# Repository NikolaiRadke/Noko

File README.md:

The DIY-**Noko Monster**, lovely and naughty, ready to build on your own. And everyone is invited to **contribute**. Noko is for everyone. What's new? See the [newsblog](https://github.com/NikolaiRadke/Noko/tree/master/NEWS.md).  

> [!NOTE]
> This Repository is not maintained anymore. 

Noko is a multifunctional monster with an ATmega328  microcontroller on an **Arduino Nano**, display, clock, radio, mp3 player, four buttons as user interface, battery, voice set and  tons of gimmicks, packed in a cuddly monster suit - sturdy,
lovely and sometimes a bit mean and annoying. Just the way you want him to be. He, she or it - this is your decision     and only depends on the voice set. In this repository Noko is a lad, a real bloke! A buddy for life and a companion by day and night. All he needs is a little power every now and then.  

**Noko** stands for **No**ra and ni**ko**'s monster.

### Notes for non-German Noko makers
There are a German and an English version. Right now, the building wiki, the voice set, the manual and the optional EEPROM text files are in German. I'll try to translate the wiki and the manual one day. Until then, feel free to ask me for translation, if you need help. **Contribute!** I need an English voice set and English text files. In addition, any other language is welcome, Noko is to be cosmopolitan!

### Prerequisites
Noko needs Arduino IDE 1.6.6 - [1.8.2](https://www.arduino.cc/en/Main/Software) Copy the folder `Noko/V10/src/[language]/Noko/` into your sketch folder. When using 1.6.10 or newer with AVR core 1.6.12 or newer, everything will compile out-of-the-box. With 1.6.9 or lower, *Noko.ino* won't compile, the sketch size is too large. 

**Option 1:** Install newest  [IDE](https://www.arduino.cc/en/Main/Software) and relax.  
**Option 2:** If you are using IDE 1.6.9 or lower, you need to install [Optiboot](https://github.com/Optiboot/optiboot) onto your Nano.  
**Option 3:** Take one of the precompiled hex-files and follow the instructions in [how to compile](https://github.com/NikolaiRadke/Noko/tree/master/howto_compile).  

**In any case, Optiboot is strongly recommended.**

### Content

```
Noko/
├── howto_compile/
|   Manual how compile the sketches in your Arduino IDE and precompiled sketches.  
|   └── precompiled/
|       Precompiled hex-files and windows tools.
|       ├── Deutsch/
|       |   German Versions.
|       ├── English/
|       |   English Versions.
|       ├── Flashtool/
|       |   Linux firmware flasher.
|       └── avrdude_win/
|           Avrdude files for windows.
|
├── manual/
|   Noko manual in PDF format and a template for a packaging design.
|   └── scribus/
|       Source documents for Scribus with all illustrations and fonts.
|
├── mp3/
|   Female and male voice sets for Noko in German. English needed? Contribute!
|   ├── female/  
|   |   Female voice set for Nokos.
|   |   └── VoiceSet_226/
|   |       New voice files.
|   └── male/
|       Male voice sets
|       ├── alternative/
|       |   Some less rude voice files.
|       ├── VoiceSet_111/
|       |   Voice set for older Nokos.
|       └── VoiceSet_226/
|           Enhanced voice set.
| 
├── schematics/
|   The Schematics for the Noko parts, the Noko sewing pattern and shopping lists.
|   └── geda/
|       Source documents for gEDA.
|
├── src/
|   Arduino sketches.
|   ├── deutsch/
|   |   German version
|   |   └── Noko/
|   |       Main sourcecode with all the required libraries.
|   ├── english/
|   |   English version. 
|   |   └── Noko/
|   |       Same files but translated. 
|   └── tools/
|       Tools for using components and diagnostic.    
|       ├── I2C-Scanner/
|       |   Sketch to scan adresses of all connected I2C-devices.
|       ├── Noko_Diagnostics/
|       |   Tool to test Noko functions via serial monitor.
|       ├── Noko_Disk1/
|       |   Sketch to write the Disk1 textfile into 24LC256-EEPROMs.
|       ├── Noko_EEPROM_Disk0/
|       |   Sketch to write Noko presets into the Arduino EEPROM and the Disk0 textfile into the
|       |   AH24C32 EEPROM.
|       └── Noko_Time/
|           Simple tool to set the current time without touching the EEPROM
└── write_EEPROM/
    Tools to write data through serial connection to the Arduino and the EEPROMs. 
```
### Let's get started!

Interested in Noko? Great! Let's start here: [German wiki](https://github.com/NikolaiRadke/Noko/wiki).  
English wiki will follow. One day...

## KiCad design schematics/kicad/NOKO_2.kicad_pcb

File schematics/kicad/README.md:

Achtung! Bitte die Gerber Dateien noch nicht benutzen! Es müssen noch Fehler beseitigt werden.

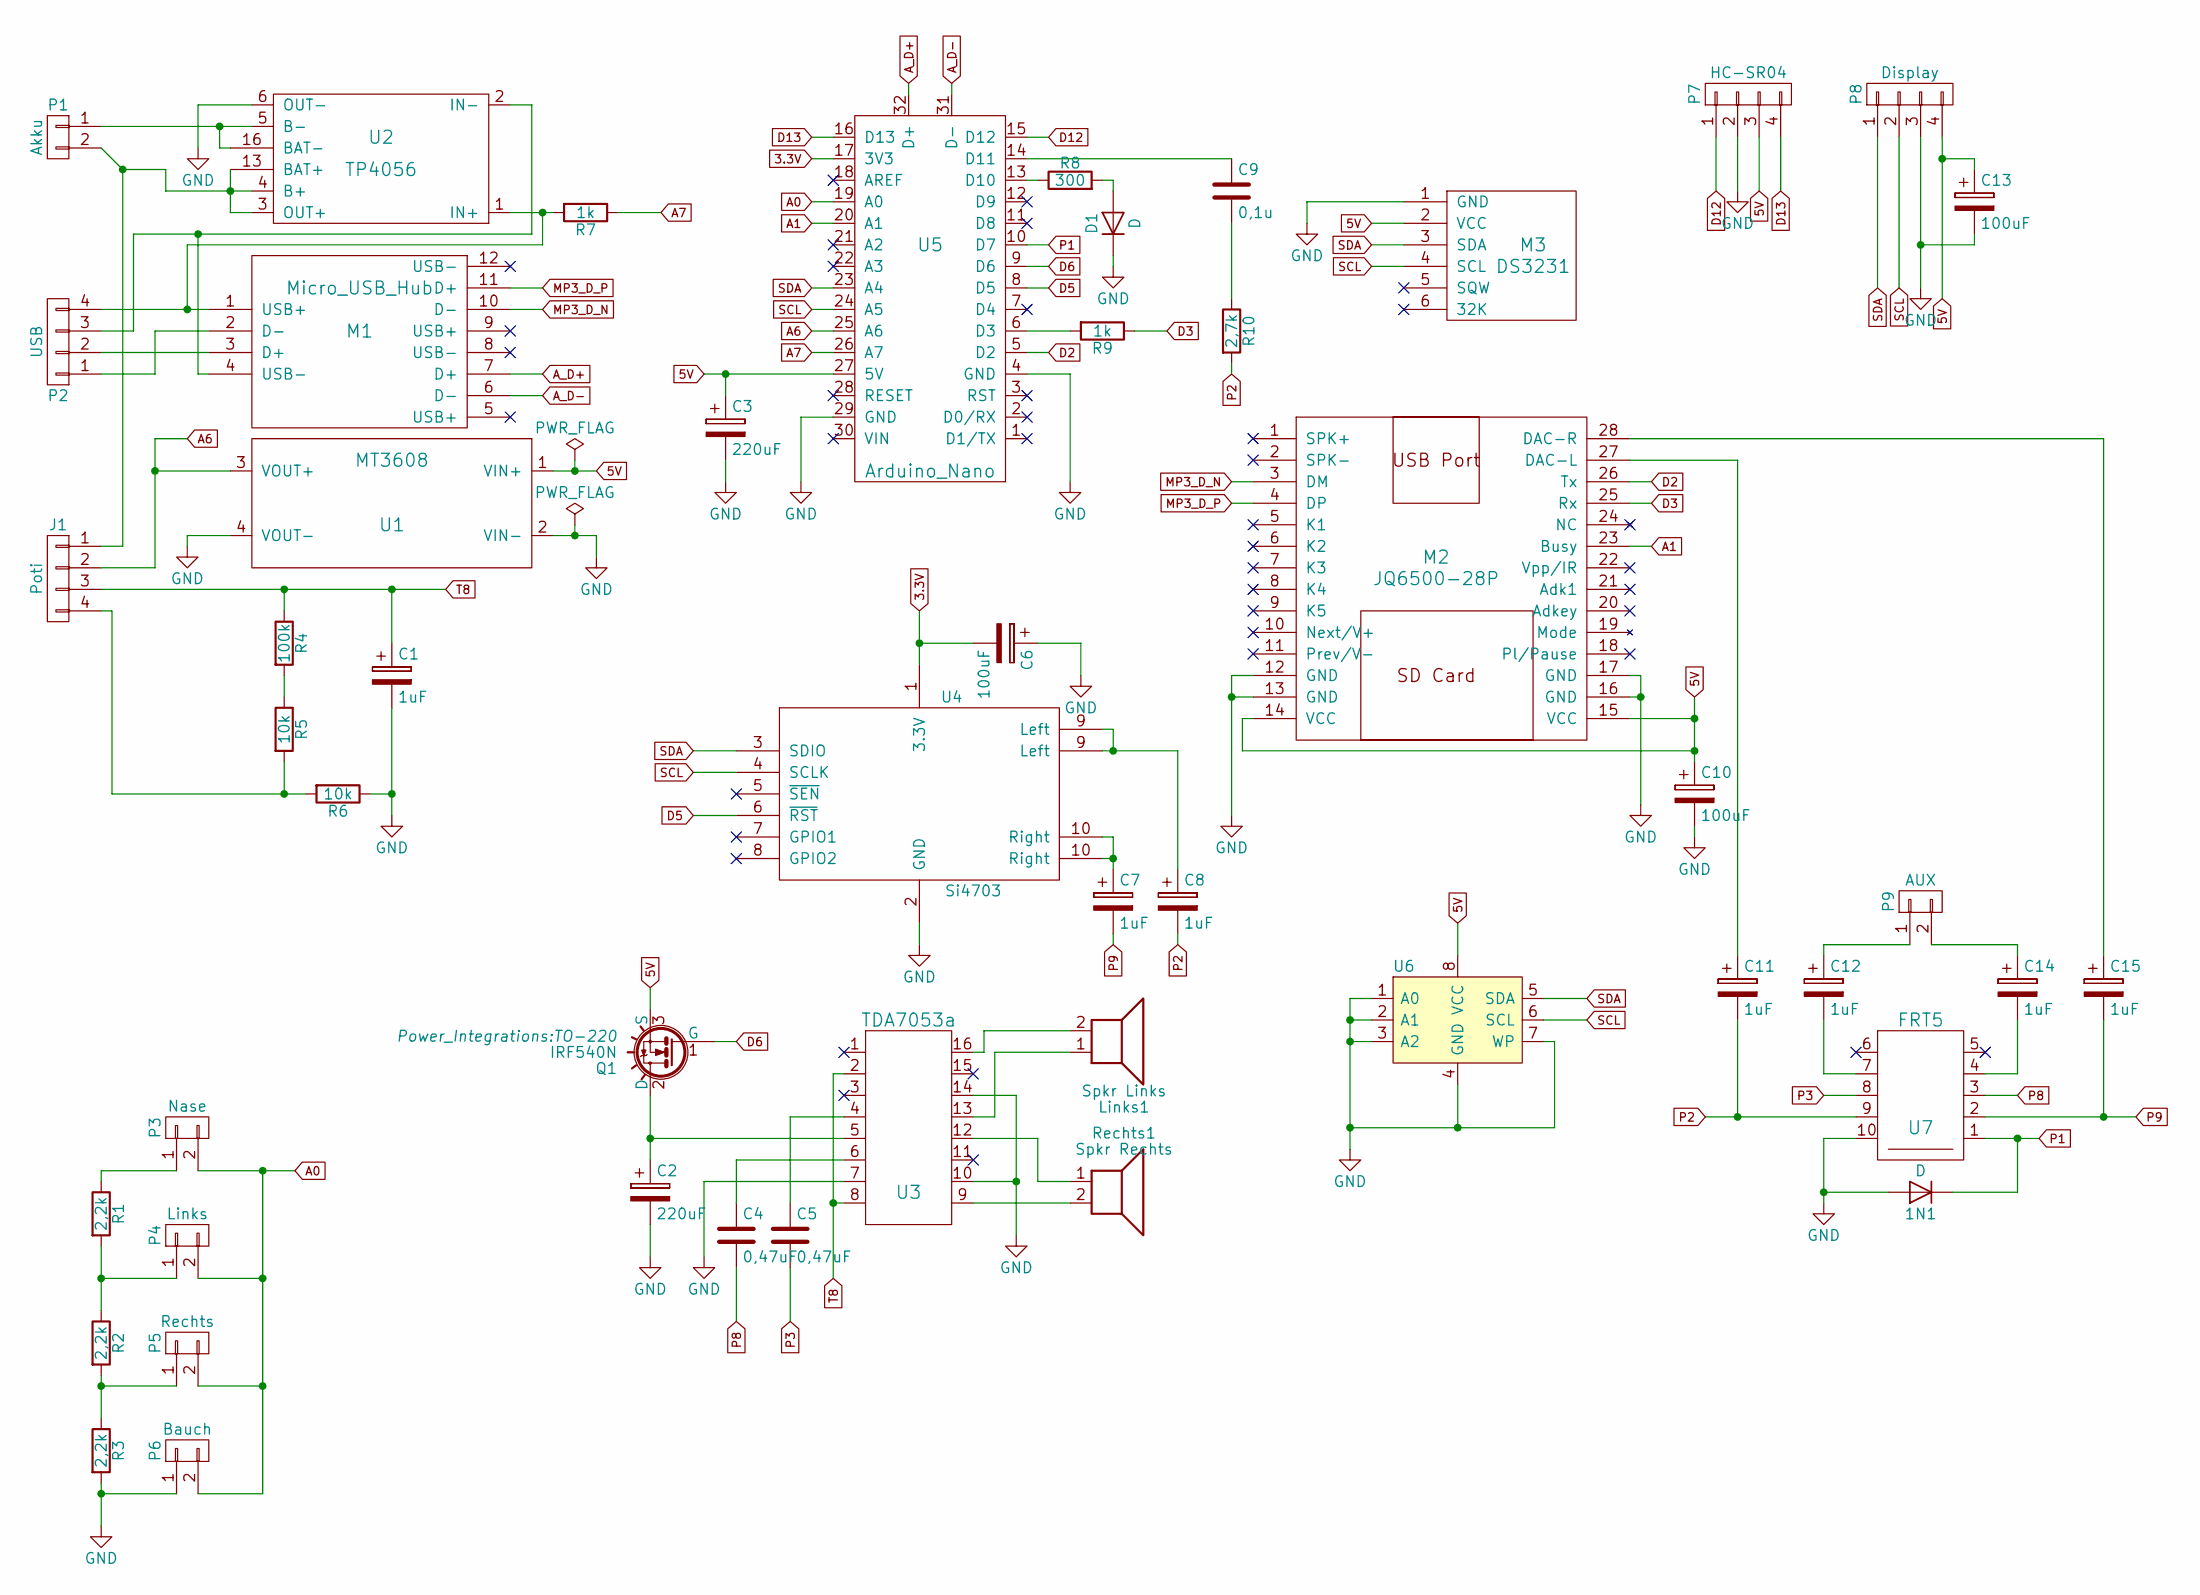
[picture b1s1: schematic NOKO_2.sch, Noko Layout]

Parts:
1N1: D; D_DO-41_SOD81_P7.62mm_Horizontal
C1, C11: 1uF; CP_Radial_D5.0mm_P2.50mm
C2, C3: 220uF; CP_Radial_D8.0mm_P3.80mm
C4, C5: 0,47uF; C_Disc_D3.4mm_W2.1mm_P2.50mm
C6, C10, C13: 100uF; CP_Radial_D5.0mm_P2.50mm
C7, C8, C12, C14, C15: 1uF; CP_Radial_D5.0mm_P2.00mm
C9: 0,1u; C_Disc_D3.4mm_W2.1mm_P2.50mm
D1: D; JST_XH_B02B-XH-A_02x2.50mm_Straight
J1: Poti; JST_XH_B04B-XH-A_04x2.50mm_Straight
Links1: Spkr Links; JST_XH_B02B-XH-A_02x2.50mm_Straight
M1: Micro_USB_Hub; Micro-USB-Hub
M2: JQ6500-28P
M3: DS3231
P1: Akku; JST_XH_B02B-XH-A_02x2.50mm_Straight
P2: USB; JST_XH_B04B-XH-A_04x2.50mm_Straight
P3: Nase; JST_XH_B02B-XH-A_02x2.50mm_Straight
P4: Links; JST_XH_B02B-XH-A_02x2.50mm_Straight
P5: Rechts; JST_XH_B02B-XH-A_02x2.50mm_Straight
P6: Bauch; JST_XH_B02B-XH-A_02x2.50mm_Straight
P7: HC-SR04; JST_XH_B04B-XH-A_04x2.50mm_Straight
P8: Display; JST_XH_B04B-XH-A_04x2.50mm_Straight
P9: AUX; JST_XH_B02B-XH-A_02x2.50mm_Straight
Q1: IRF540N; TO-220
R1, R2, R3: 2,2k; R_Axial_DIN0207_L6.3mm_D2.5mm_P7.62mm_Horizontal
R4: 100k; R_Axial_DIN0207_L6.3mm_D2.5mm_P7.62mm_Horizontal
R5, R6: 10k; R_Axial_DIN0207_L6.3mm_D2.5mm_P7.62mm_Horizontal
R7, R9: 1k; R_Axial_DIN0207_L6.3mm_D2.5mm_P7.62mm_Horizontal
R8: 300; R_Axial_DIN0207_L6.3mm_D2.5mm_P7.62mm_Horizontal
R10: 2,7k; R_Axial_DIN0207_L6.3mm_D2.5mm_P7.62mm_Horizontal
Rechts1: Spkr Rechts; JST_XH_B02B-XH-A_02x2.50mm_Straight
U1: MT3608
U2: TP4056
U3: TDA7053a
U4: Si4703
U5: Arduino_Nano
U6: 24LC256; DIP-8_W7.62mm
U7: FRT5; Printrelais_ST03

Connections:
3.3V: C6.2, U4.1 (3.3V), U5.17 (3V3)
A0: P3.2, P4.2, P5.2, P6.2, U5.19 (A0)
A1: M2.23 (Busy), U5.20 (A1)
A7: R7.1, U5.26 (A7)
A_D+: M1.7 (D+), U5.32 (D+)
A_D-: M1.6 (D-), U5.31 (D-)
D2: M2.26 (Tx), U5.5 (D2)
D3: M2.25 (Rx), R9.1
D5: U4.6 (~RST), U5.8 (D5)
D6: Q1.1 (G), U5.9 (D6)
D12: P7.1, U5.15 (D12)
D13: P7.4, U5.16 (D13)
GND: 1N1.2 (A), C1.2, C2.2, C3.2, C6.1, C10.2, C13.2, D1.1 (K), M2.12 (GND), M2.13 (GND), M2.16 (GND), M2.17 (GND), M3.1 (GND), P6.1, P7.2, P8.3, R3.2, R6.1, U1.2 (VIN-), U1.4 (VOUT-), U2.6 (OUT-), U3.7, U3.10, U3.14, U4.2 (GND), U5.4 (GND), U5.29 (GND), U6.1 (A0), U6.2 (A1), U6.3 (A2), U6.4 (GND), U6.7 (WP), U7.10
MP3_D_N: M1.10 (D-), M2.3 (DM)
MP3_D_P: M1.11 (D+), M2.4 (DP)
unnamed: C2.1, Q1.2 (D), U3.5
unnamed: C4.1, U3.6
unnamed: C5.1, U3.4
unnamed: C7.1, U4.10 (Right)
unnamed: C8.1, U4.9 (Left)
unnamed: C9.1, U5.14 (D11)
unnamed: C9.2, R10.1
unnamed: C11.1, M2.27 (DAC-L)
unnamed: C12.1, P9.1
unnamed: C12.2, U7.7
unnamed: C14.1, P9.2
unnamed: C14.2, U7.4
unnamed: C15.1, M2.28 (DAC-R)
unnamed: D1.2 (A), R8.2
unnamed: J1.1, P1.2, U2.3 (OUT+), U2.4 (B+), U2.13 (BAT+)
unnamed: J1.4, R5.2, R6.2
unnamed: Links1.1, U3.13
unnamed: Links1.2, U3.16
unnamed: M1.1 (USB+), P2.4, R7.2, U2.1 (IN+)
unnamed: M1.2 (D-), P2.1
unnamed: M1.3 (D+), P2.2
unnamed: M1.4 (USB-), P2.3, U2.2 (IN-)
unnamed: P1.1, U2.5 (B-), U2.16 (BAT-)
unnamed: P3.1, R1.1
unnamed: P4.1, R1.2, R2.1
unnamed: P5.1, R2.2, R3.1
unnamed: R4.2, R5.1
unnamed: R8.1, U5.13 (D10)
unnamed: R9.2, U5.6 (D3)
unnamed: Rechts1.1, U3.12
unnamed: Rechts1.2, U3.9
P1: 1N1.1 (K), U5.10 (D7), U7.1
P2: C8.2, C11.2, R10.2, U7.9
P3: C5.2, U7.8
P8: C4.2, U7.3
P9: C7.2, C15.2, U7.2
SCL: M3.4 (SCL), P8.2, U4.4 (SCLK), U5.24 (A5), U6.6 (SCL)
SDA: M3.3 (SDA), P8.1, U4.3 (SDIO), U5.23 (A4), U6.5 (SDA)
T8: C1.1, J1.3, R4.1, U3.2, U3.8

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
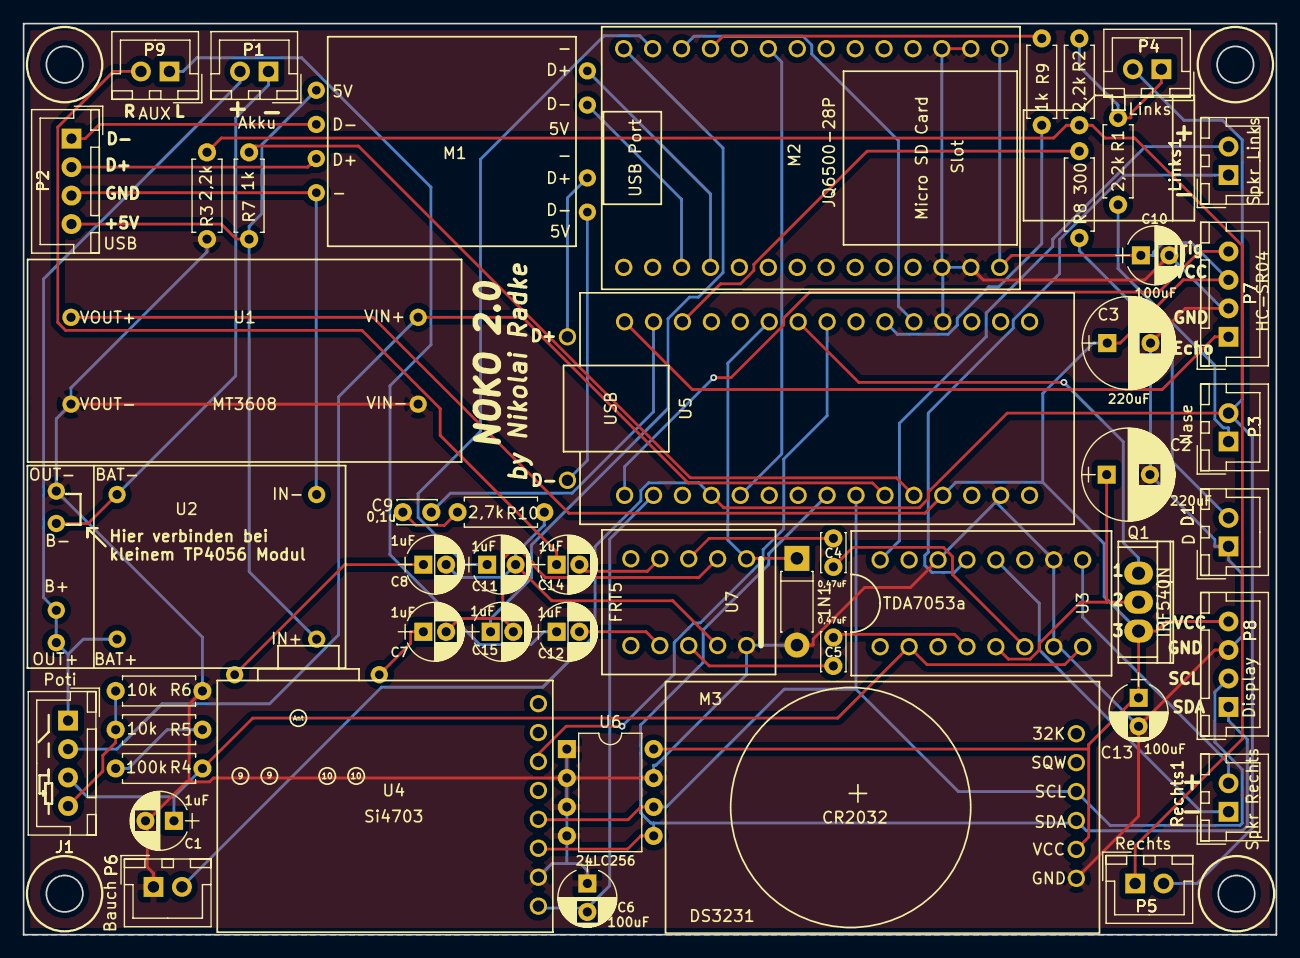
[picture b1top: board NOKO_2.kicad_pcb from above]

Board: 2 copper layers, 110.0 x 80.0 mm, 50 parts (0 on the bottom side), 56 nets.

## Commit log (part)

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2017-04-28 removed useless platform.txt
2017-04-30 Code cleanup and more Time.h compatibility
2017-05-01 Sysinfo now optional
2017-05-01 New LCD library. 770 more bytes free
2017-05-02 Small code cleanup
2017-05-02 Firmware 010517
2017-05-11 Small comment update
2017-05-15 Sorcecode internationalization
2017-05-15 PROGMEM bugfix
2017-05-15 Uploaded precompiled 010517 files
2017-05-17 Firmware 170517
2017-05-17 New precompiled 170517 firmware
2017-05-21 RDS rework. Works MUCH better now!
2017-05-21 Firmware 1.0-210517
2017-05-28 Added Linux GUI update tool
2017-05-28 Clean up
2017-05-29 Added port selector
2017-05-29 Added Optiboot selector
2017-05-30 Better file handling
2017-05-31 Small flash size improvement
2017-05-31 New tool directory with new diagnistic tool
2017-05-31 Added some error handling
2017-05-31 Renamed directory
2017-06-04 Some code shrinking
2017-06-04 Ouh! Found a distance light settings bug!
2017-06-04 More code shrinking
2017-06-04 Spellchecking
2017-06-09 Fixed a bug: Display won't turn off
2017-06-19 Firmware 1.0-190617
2017-06-24 Firmware 1.0-24062017
2017-06-27 New eagle layout for a better NOKO
2017-06-30 Firmware 1.0-300617
2017-06-30 Added precompiled 300617 firmwares
2017-07-04 New PCB schematics
2017-07-13 New poti schematic
2017-07-20 Updated diagnostic tool
2017-07-21 NOKO Diagnostics V0.5
2017-07-24 Added layout drill file
2017-08-24 Small changes in settings sketches
2017-08-24 Firmware 280717 - fixed a bug that limited the number of stories to 42 instead of 95
2017-09-21 Small update: Changed EEPROM.write() to EEPROM.update() to save EEPROM lifetime
2017-10-07 Some code enhancements and a better diagnostics tool
2017-10-31 New power schematics picture
2017-10-31 New main board downside schematic
2017-11-10 Small variable renamed
2017-11-11 New schematics for the upper board. Two cuts were missing.
2017-11-30 Reworked story adressing. Working now.
2017-12-13 Added precompiled 301117 firmwares
2017-12-13 Removed unused precompiled files
2017-12-18 Added pcb gerber-files
2017-12-25 PCB: Bestückungsliste hinzugefügt
2017-12-29 Set .gitattributes
2017-12-30 Added option to read the busy signal analog at A1
2017-12-30 Very small fixes
2018-01-02 New rendered PDF manual
2018-01-08 Firmware 080118 with enhanced voice set suppoert
2018-01-08 Fixed some small bugs
2018-01-08 Fixed small typos
2018-01-09 GitHub cleanup
2018-01-12 Added time setting tool
2018-01-13 New voice set support
2018-01-15 Added new pcb files
2018-01-15 Story menu no shows length in hours and minutes
2018-01-16 Renamed EEPROM from wring AH23C32 to correct AT24C32
2018-01-23 NOKO.ino is working again
2018-01-24 added kicad folder with rotated arduino
2018-01-24 created Gerber files
2018-01-26 Changed module descriptors to F-Silk layer
2018-01-27 Fixed wrong comments
2018-01-27 last changes
2018-01-27 Gerber files updated
2018-01-28 added D+ / D- to Arduino USB pads
2018-01-29 need to change circuit again, don't use at the moment
2018-01-29 Footprint für Arduino optimiert, so dass er besser passt
2018-01-30 Improved diagnostics tool V0.7
2018-01-30 beautified mounting holes, change folder structure to make more sense
2018-01-30 created PDF folder
2018-01-30 updated circuit diagram in PDF folder
2018-01-30 deleted old circuit diagram
2018-02-01 changed layout of USB hub, fixed mix up of D+ and D- line to MP3 module
2018-02-03 Improved diagnostics tools V0.8
2018-02-06 Added PCB V2.0 Firmware and renamed some mp3s to correct format
2018-02-08 Reworked some tone code
2018-02-09 New Firmware 090218 - New tone library!
2018-02-11 Schutzdiode am Relais umgedreht
2018-02-23 New Firmware 1.0+2.0_ 230218
2018-02-23 Speed up playing interface
2018-02-23 New eeprom programming files for V2.0
2018-02-24 New Firmware 2.0-240218
2018-02-24 Aufschrift auf 2.0 geändert
2018-02-25 Removed obsolete folder pcb
2018-02-26 Firmware 2.0-240218. Fixed wrong story adressing
2018-02-27 Firmware 2.0-270218
2018-02-28 Firmware 1.0-280218 - Old NOKO gehts the equalizer too.
2018-03-01 Few changes in EEPROM tools for V1.0
2018-03-01 Updated EEPROM tools
2018-03-01 Updated german manual
2018-03-02 Firmware X.0-020318
2018-03-02 Cleanup
2018-03-02 keine Aenderung!
2018-03-07 Firmware X.0-070318
2018-03-07 Updated settings tools
2018-03-12 project file update
2018-03-13 Updated manual
2018-03-16 VIN+ und VOUT+ des StepUp Moduls richtig / gedreht
2018-03-17 Last, last, last changes
2018-03-17 Jetzt auch mit GERBER Dateien inklusive ZIP Datei Update!
2018-03-19 Added Umlaute-support :-)
2018-04-06 Firmware X.0-060418
2018-04-30 Slightly optimized random generator
2018-04-30 Code cleanup
2018-05-09 Oops - removed useless debugging event tester
2018-05-11 New female voice set
2018-05-11 New folder name
2018-05-15 Reset presets in NOKO.ino
2018-05-23 New backpart
2018-08-26 New IDE 1.8.6 used
2018-10-31 Tested with AVR Core 1.6.23
2018-11-20 Cleanup and small bugfixes
2019-04-16 Firmware 140419. Fixed old and rare night mode bug
2019-09-18 Tested IDE 1.8.10
2020-06-14 Reworking repository
2020-07-11 Repository rework
2026-04-12 Update README to reflect repository maintenance status
    Added a note indicating that the repository is no longer maintained.
